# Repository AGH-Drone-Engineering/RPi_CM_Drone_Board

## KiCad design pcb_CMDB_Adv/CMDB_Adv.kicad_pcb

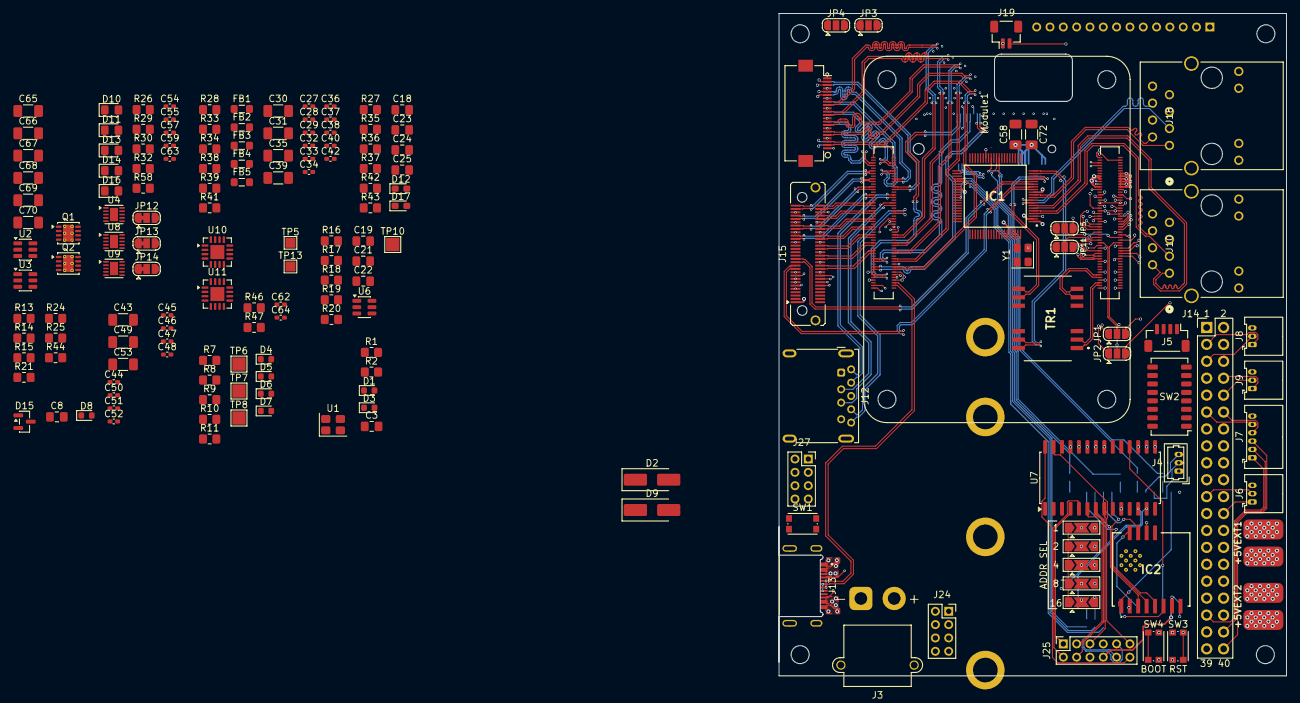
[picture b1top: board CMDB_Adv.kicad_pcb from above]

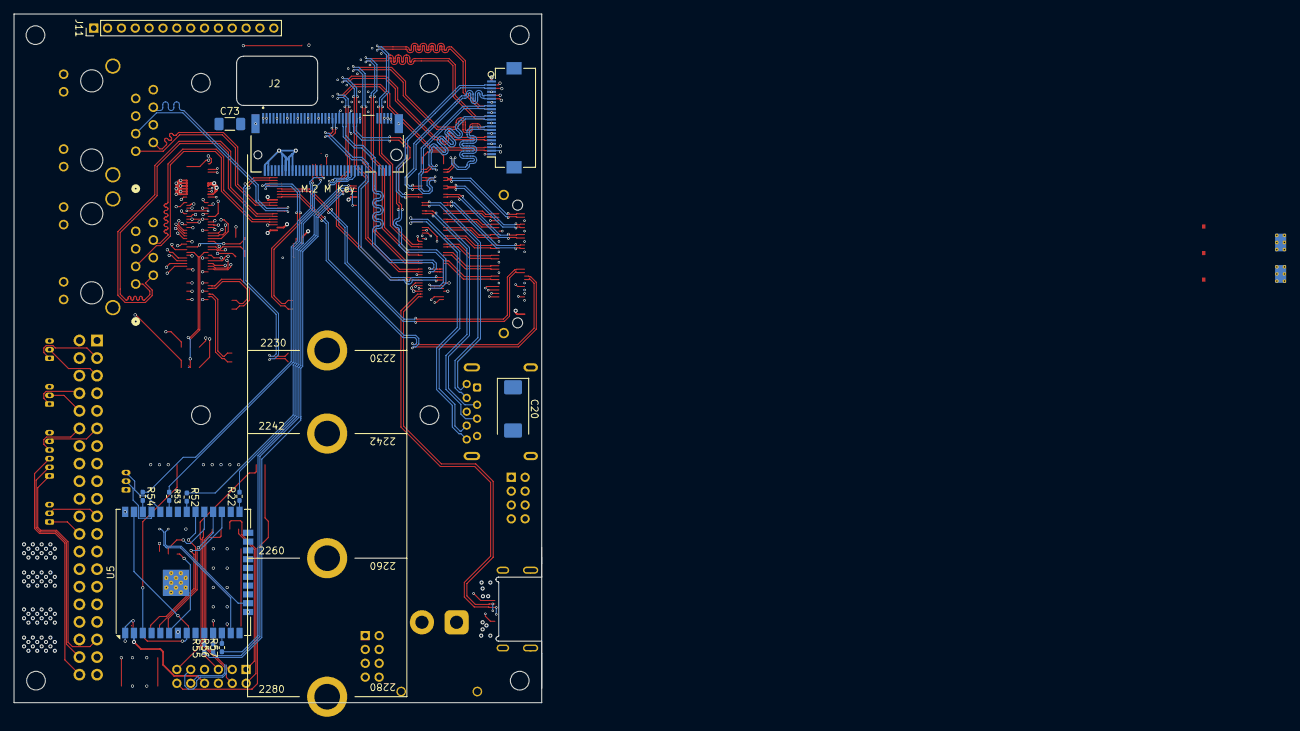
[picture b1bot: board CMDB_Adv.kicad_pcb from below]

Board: 6 copper layers, 76.2 x 99.4 mm, 190 parts (13 on the bottom side), 277 nets.

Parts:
C3, C18, C23, C24, C25: 100n; C_0805_2012Metric_Pad1.18x1.45mm_HandSolder
C8: 470nF; C_0805_2012Metric_Pad1.18x1.45mm_HandSolder
C19, C21, C22: 10u; C_0805_2012Metric_Pad1.18x1.45mm_HandSolder
C20: 100uF; CP_EIA-7343-31_Kemet-D
C27, C28, C29, C32, C33, C34, C36, C37, C38, C40, C42, C44, C45, C46, C47, C48, C50, C51, C52, C54, C55, C57, C59, C62, C63, C64: 100nF; C_0402_1005Metric_Pad0.74x0.62mm_HandSolder
C30, C31, C35, C39, C43, C49, C58, C72, C73: 22uF; C_1206_3216Metric_Pad1.33x1.80mm_HandSolder
C53, C65, C66, C67, C68, C69, C70: 10uF; C_1206_3216Metric_Pad1.33x1.80mm_HandSolder
D1, D8: LED Green; LED_0603_1608Metric
D2, D9: SS34; D_SMA_Handsoldering
D3: LED Red; LED_0603_1608Metric
D4, D6: GREEN; LED_0603_1608Metric
D5: RED; LED_0603_1608Metric
D7: AMBER; LED_0603_1608Metric
D10: PWR_VALID; D_0805_2012Metric_Pad1.15x1.40mm_HandSolder
D11: +5VPB; D_0805_2012Metric_Pad1.15x1.40mm_HandSolder
D12: ETH4_Y; LED_0603_1608Metric_Pad1.05x0.95mm_HandSolder
D13: +5VEXT1; D_0805_2012Metric_Pad1.15x1.40mm_HandSolder
D14: +5VEXT2; D_0805_2012Metric_Pad1.15x1.40mm_HandSolder
D15: BAT54A; SOT-23
D16: +VIMM; D_0805_2012Metric_Pad1.15x1.40mm_HandSolder
D17: ETH4_G; LED_0603_1608Metric_Pad1.05x0.95mm_HandSolder
FB1, FB2, FB3, FB4, FB5: BLM21PG221SN1D; L_0805_2012Metric_Pad1.05x1.20mm_HandSolder
H1, H2, H3, H4: MountingHole; MountingHole_2.7mm_M2.5_DIN965
IC1: KSZ8795CLXCC; QFP40P1200X1200X160-80N
IC2: Wio-SX1262
J2: Bus_M.2_Socket_M; M.2_M_Key_socket_2280
J3: CONN_VIN; AMASS_XT30PW-M_1x02_P2.50mm_Horizontal
J4: J_ESP_DBG_UART; Molex_PicoBlade_53047-0310_1x03_P1.25mm_Vertical
J5: CONN_FAN; JST_SH_BM04B-SRSS-TB_1x04-1MP_P1.00mm_Vertical
J6: CONN_UART2; Molex_PicoBlade_53048-0310_1x03_P1.25mm_Horizontal
J7: CONN_SPI1; Molex_PicoBlade_53048-0610_1x06_P1.25mm_Horizontal
J8: CONN_I2C1; Molex_PicoBlade_53048-0310_1x03_P1.25mm_Horizontal
J9: CONN_UART0; Molex_PicoBlade_53048-0310_1x03_P1.25mm_Horizontal
J10: ETH1; CONN12_ARJM11B1-009-AB-EW2_ABR
J11: CONN_SDIO; PinHeader_1x14_P2.00mm_Vertical
J12: CONN_USB3_A; USB3_A_Molex_48393-001
J13: CONN_USB_PWR_OTG; GCT_USB4510-03-1-A_REVA
J14: CONN_HAT; PinHeader_2x20_P2.54mm_Vertical
J15: CONN_DOCK; Samtec_LSHM-130-xx.x-x-DV-S_2x30-1SH_P0.50mm_Vertical
J16: CONN_CAM1; Hirose_FH12-22S-0.5SH_1x22-1MP_P0.50mm_Horizontal
J17: CONN_CAM0; Hirose_FH12-22S-0.5SH_1x22-1MP_P0.50mm_Horizontal
J18: ETH2; CONN12_ARJM11B1-009-AB-EW2_ABR
J19: CONN_RTC; JST_SH_BM02B-SRSS-TB_1x02-1MP_P1.00mm_Vertical
J20: CONN_5VEXT1; SolderWirePad_1x01_SMD_3x6mm
J21: CONN_5VEXT1_GND; SolderWirePad_1x01_SMD_3x6mm
J22: CONN_5VEXT2; SolderWirePad_1x01_SMD_3x6mm
J23: CONN_5VEXT2_GND; SolderWirePad_1x01_SMD_3x6mm
J24: AUX_PWR_OUT1; PinSocket_2x04_P2.00mm_Vertical
J25: PL_CTRL_IO; PinSocket_2x06_P2.00mm_Vertical
J27: AUX_PWR_OUT2; PinSocket_2x04_P2.00mm_Vertical
JP1: GPIO0_SEL; SolderJumper-3_P1.3mm_Open_RoundedPad1.0x1.5mm
JP2: GPIO1_SEL; SolderJumper-3_P1.3mm_Open_RoundedPad1.0x1.5mm
JP3: ETH_Y_SEL; SolderJumper-3_P1.3mm_Open_RoundedPad1.0x1.5mm
JP4: ETH_G_SEL; SolderJumper-3_P1.3mm_Open_RoundedPad1.0x1.5mm
JP5: GPIO8_SEL; SolderJumper-3_P1.3mm_Open_RoundedPad1.0x1.5mm
JP6: ADDR1; SolderJumper-3_P2.0mm_Open_TrianglePad1.0x1.5mm
JP7: ADDR2; SolderJumper-3_P2.0mm_Open_TrianglePad1.0x1.5mm
JP8: ADDR4; SolderJumper-3_P2.0mm_Open_TrianglePad1.0x1.5mm
JP9: ADDR8; SolderJumper-3_P2.0mm_Open_TrianglePad1.0x1.5mm
JP10: ADDR16; SolderJumper-3_P2.0mm_Open_TrianglePad1.0x1.5mm
JP11: GPIO9_SEL; SolderJumper-3_P1.3mm_Open_RoundedPad1.0x1.5mm
JP12: +3V3PB2 DIS; SolderJumper-3_P1.3mm_Bridged12_RoundedPad1.0x1.5mm
JP13: +3V3PB3 DIS; SolderJumper-3_P1.3mm_Bridged12_RoundedPad1.0x1.5mm
JP14: +1V2PB DIS; SolderJumper-3_P1.3mm_Bridged12_RoundedPad1.0x1.5mm
Module1: ComputeModule5-CM5; Raspberry-Pi-5-Compute-Module
Q1, Q2: AON7534; DFN-8-1EP_3x3mm_P0.65mm_EP1.6x2.56mm_ThermalVias
R1, R2, R7, R8, R9, R10, R13, R21, R26, R29, R30, R32, R34, R39, R41, R42, R43, R46, R47, R58: 1K; R_0805_2012Metric_Pad1.20x1.40mm_HandSolder
R11, R44: 10K; R_0805_2012Metric_Pad1.20x1.40mm_HandSolder
R14, R15, R38: 4K7; R_0805_2012Metric_Pad1.20x1.40mm_HandSolder
R16, R18, R19, R20: 2.2K; R_0805_2012Metric_Pad1.20x1.40mm_HandSolder
R17: 15K; R_0805_2012Metric_Pad1.20x1.40mm_HandSolder
R22, R52, R53, R54, R55, R56, R57: 22R; R_0402_1005Metric_Pad0.72x0.64mm_HandSolder
R24, R25: 2K2; R_0805_2012Metric_Pad1.20x1.40mm_HandSolder
R27, R35, R36, R37: 220R; R_0805_2012Metric_Pad1.20x1.40mm_HandSolder
R28: 12K4 1%; R_0805_2012Metric_Pad1.20x1.40mm_HandSolder
R33: 330R; R_0805_2012Metric_Pad1.20x1.40mm_HandSolder
SW1: BT_PWR; SW_Push_1P1T_NO_CK_KMR2
SW2: SW_CONFIG; SW_DIP_SPSTx08_Slide_Copal_CHS-08A_W5.08mm_P1.27mm_JPin
SW3: SW_RESET; SW_Push_1P1T_NO_CK_KMR2
SW4: SW_BOOT; SW_Push_1P1T_NO_CK_KMR2
TP5: PWR_VALID0; TestPoint_Pad_1.5x1.5mm
TP6: +3V3 RPi; TestPoint_Pad_2.0x2.0mm
TP7: TP nPWR; TestPoint_Pad_2.0x2.0mm
TP8: TP nACT; TestPoint_Pad_2.0x2.0mm
TP10: TP VBUS_USB; TestPoint_Pad_2.0x2.0mm
TP13: PWR_VALID1; TestPoint_Pad_1.5x1.5mm
TR1: ALANL100X1-DE12DT; ALANL100X1DE12DT
U1: ASEK-32.768KHZ-L-R-T; Crystal_SMD_3225-4Pin_3.2x2.5mm
U2, U3: LM74700; SOT-23-6
U4, U8, U9: TPS7A91; Texas_S-PDSO-N10_EP1.2x2mm
U5: ESP32-WROOM-32UE
U6: AP22653W6; SOT-23-6
U7: MCP23017_SO; SOIC-28W_7.5x17.9mm_P1.27mm
U10, U11: INA3221; Texas_RGV0016A_VQFN-16-1EP_4x4mm_P0.65mm_EP2.1x2.1mm
Y1: ASE-25.000MHZ-LC-T; Oscillator_SMD_Abracon_ASE-4Pin_3.2x2.5mm

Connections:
/+1V2PB: C66.1, FB3.1, FB4.1, U9.1 (OUT), U9.2 (OUT)
/+3V3PB1: C3.1, C58.2, C72.2, C73.2, D1.2 (A), D3.2 (A), J2.2 (3.3V), J2.4 (3.3V), J2.12 (3.3V), J2.14 (3.3V), J2.16 (3.3V), J2.18 (3.3V), J2.70 (3.3V), J2.72 (3.3V), J2.74 (3.3V), U1.1 (EN), U1.4 (VDD)
/+3V3PB2: C49.2, C50.2, C51.2, C52.2, C67.1, D15.1, FB1.1, FB2.1, J25.8, R13.1, R14.1, R15.1, R24.1, R25.1, R44.2, U4.1 (OUT), U4.2 (OUT), U5.2 (VDD), U7.9 (V_{DD})
/+3V3PB3: C43.2, C44.2, C68.1, IC2.8 (VCC), U8.1 (OUT), U8.2 (OUT)
/+5VEXT1: D13.2 (A), J20.1 (Pin_1_1)
/+5VEXT2: D14.2 (A), J22.1 (Pin_1_1)
/+5VPB: C19.1, D11.2 (A), J5.1, J14.2, J14.4, J15.1, Module1.77 (+5v_(Input)), Module1.79 (+5v_(Input)), Module1.81 (+5v_(Input)), Module1.83 (+5v_(Input)), Module1.85 (+5v_(Input)), Module1.87 (+5v_(Input)), Q1.1 (D), Q2.1 (D), U2.4 (CATHODE), U3.4 (CATHODE), U6.1 (IN)
/+VBUS_USBC: C55.2, D2.2 (A), J13.A4_B9 (VBUS), J13.B4_A9 (VBUS), Q2.3 (S), R16.1, U3.3 (EN), U3.6 (ANODE)
/CM5/+3V3RPi: D4.2 (A), D5.2 (A), D6.2 (A), D7.2 (A), J11.1, J14.1, J14.17, J15.3, J16.22, J17.22, Module1.78 (GPIO_VREF(1.8v/3.3v_Input)), Module1.84 (+3.3v_(Output)), Module1.86 (+3.3v_(Output)), R11.1, R18.2, R19.2, R20.1, R27.2, R35.2, R36.2, R37.2, R42.2, R43.2, TP6.1 (1_1)
/CM5/+3V3STB: J19.2, Module1.76 (VBAT)
/CM5/BT_nDis: Module1.91 (BT_nDisable), SW2.11
/CM5/CAM0_GPIO0: J17.17, Module1.97 (CAM_GPIO0)
/CM5/CAM0_GPIO1: J17.18, Module1.100 (CAM_GPIO1)
/CM5/EEPROM_nWP: Module1.20 (EEPROM_nWP), SW2.15
/CM5/ETH.P0_N: Module1.10 (Ethernet_Pair0_N), TR1.6 (RD-)
/CM5/ETH.P0_P: Module1.12 (Ethernet_Pair0_P), TR1.5 (RD+)
/CM5/ETH.P1_N: Module1.6 (Ethernet_Pair1_N), TR1.2 (TD-)
/CM5/ETH.P1_P: Module1.4 (Ethernet_Pair1_P), TR1.1 (TD+)
/CM5/ETH_LED_G: JP4.2 (C), R9.2
/CM5/ETH_LED_Y: JP3.2 (C), R10.2
/CM5/FAN_PWM: J5.2, Module1.19 (FAN_PWM), R11.2
/CM5/GP.0: J14.27, JP1.3 (B)
/CM5/GP.1: J14.28, JP2.3 (B)
/CM5/GP.2: J8.1, J14.3, Module1.58 (GPIO2)
/CM5/GP.3: J8.2, J14.5, Module1.56 (GPIO3)
/CM5/GP.4: J6.1, J14.7, Module1.54 (GPIO4)
/CM5/GP.5: J6.2, J14.29, Module1.34 (GPIO5)
/CM5/GP.6: J14.31, Module1.30 (GPIO6)
/CM5/GP.7: J14.26, Module1.37 (GPIO7)
/CM5/GP.8: J14.24, JP5.3 (B)
/CM5/GP.9: J14.21, JP11.3 (B)
/CM5/GP.10: J14.19, Module1.44 (GPIO10)
/CM5/GP.11: J14.23, Module1.38 (GPIO11)
/CM5/GP.12: J14.32, Module1.31 (GPIO12)
/CM5/GP.13: J14.33, Module1.28 (GPIO13)
/CM5/GP.14: J9.1, J14.8, Module1.55 (GPIO14)
/CM5/GP.15: J9.2, J14.10, Module1.51 (GPIO15)
/CM5/GP.16: J14.36, Module1.29 (GPIO16)
/CM5/GP.17: J7.5, J14.11, Module1.50 (GPIO17)
/CM5/GP.18: J7.4, J14.12, Module1.49 (GPIO18)
/CM5/GP.19: J7.1, J14.35, Module1.26 (GPIO19)
/CM5/GP.20: J7.2, J14.38, Module1.27 (GPIO20)
/CM5/GP.21: J7.3, J14.40, Module1.25 (GPIO21)
/CM5/GP.22: J14.15, Module1.46 (GPIO22)
/CM5/GP.23: J14.16, Module1.47 (GPIO23)
/CM5/GP.24: J14.18, Module1.45 (GPIO24)
/CM5/GP.25: J14.22, Module1.41 (GPIO25)
/CM5/GP.26: J14.37, Module1.24 (GPIO26)
/CM5/GP.27: J14.13, Module1.48 (GPIO27)
/CM5/GPIO0_RAW: JP1.2 (C), Module1.36 (ID_SD)
/CM5/GPIO1_RAW: JP2.2 (C), Module1.35 (ID_SC)
/CM5/GPIO8_RAW: JP5.2 (C), Module1.39 (GPIO8)
/CM5/GPIO9_RAW: JP11.2 (C), Module1.40 (GPIO9)
/CM5/HDMI0.CEC: J15.15, Module1.151 (HDMI0_CEC)
/CM5/HDMI0.CK_N: J15.59, Module1.190 (HDMI0_CLK_N)
/CM5/HDMI0.CK_P: J15.57, Module1.188 (HDMI0_CLK_P)
/CM5/HDMI0.D0_N: J15.53, Module1.184 (HDMI0_TX0_N)
/CM5/HDMI0.D0_P: J15.51, Module1.182 (HDMI0_TX0_P)
/CM5/HDMI0.D1_N: J15.47, Module1.178 (HDMI0_TX1_N)
/CM5/HDMI0.D1_P: J15.45, Module1.176 (HDMI0_TX1_P)
/CM5/HDMI0.D2_N: J15.41, Module1.172 (HDMI0_TX2_N)
/CM5/HDMI0.D2_P: J15.39, Module1.170 (HDMI0_TX2_P)
/CM5/HDMI0.HP: J15.17, Module1.153 (HDMI0_HOTPLUG)
/CM5/HDMI0.SCL: J15.11, Module1.200 (HDMI0_SCL)
/CM5/HDMI0.SDA: J15.13, Module1.199 (HDMI0_SDA)
/CM5/HDMI1.CEC: J15.16, Module1.149 (HDMI1_CEC)
/CM5/HDMI1.CK_N: J15.60, Module1.166 (HDMI1_CLK_N)
/CM5/HDMI1.CK_P: J15.58, Module1.164 (HDMI1_CLK_P)
/CM5/HDMI1.D0_N: J15.54, Module1.160 (HDMI1_TX0_N)
/CM5/HDMI1.D0_P: J15.52, Module1.158 (HDMI1_TX0_P)
/CM5/HDMI1.D1_N: J15.48, Module1.154 (HDMI1_TX1_N)
/CM5/HDMI1.D1_P: J15.46, Module1.152 (HDMI1_TX1_P)
/CM5/HDMI1.D2_N: J15.42, Module1.148 (HDMI1_TX2_N)
/CM5/HDMI1.D2_P: J15.40, Module1.146 (HDMI1_TX2_P)
/CM5/HDMI1.HP: J15.18, Module1.143 (HDMI1_HOTPLUG)
/CM5/HDMI1.SCL: J15.12, Module1.147 (HDMI1_SCL)
/CM5/HDMI1.SDA: J15.14, Module1.145 (HDMI1_SDA)
/CM5/MIPI0.CK_N: J17.8, Module1.127 (MIPI0_C_N)
/CM5/MIPI0.CK_P: J17.9, Module1.129 (MIPI0_C_P)
/CM5/MIPI0.D0_N: J17.2, Module1.115 (MIPI0_D0_N)
/CM5/MIPI0.D0_P: J17.3, Module1.117 (MIPI0_D0_P)
/CM5/MIPI0.D1_N: J17.5, Module1.121 (MIPI0_D1_N)
/CM5/MIPI0.D1_P: J17.6, Module1.123 (MIPI0_D1_P)
/CM5/MIPI0.D2_N: J17.11, Module1.133 (MIPI0_D2_N)
/CM5/MIPI0.D2_P: J17.12, Module1.135 (MIPI0_D2_P)
/CM5/MIPI0.D3_N: J17.14, Module1.139 (MIPI0_D3_N)
/CM5/MIPI0.D3_P: J17.15, Module1.141 (MIPI0_D3_P)
/CM5/MIPI0_ID_SCL: J17.20, Module1.80 (SCL0)
/CM5/MIPI0_ID_SDA: J17.21, Module1.82 (SDA0)
/CM5/MIPI1.CK_N: J16.8, Module1.187 (MIPI1_C_N)
/CM5/MIPI1.CK_P: J16.9, Module1.189 (MIPI1_C_P)
/CM5/MIPI1.D0_N: J16.2, Module1.175 (MIPI1_D0_N)
/CM5/MIPI1.D0_P: J16.3, Module1.177 (MIPI1_D0_P)
/CM5/MIPI1.D1_N: J16.5, Module1.181 (MIPI1_D1_N)
/CM5/MIPI1.D1_P: J16.6, Module1.183 (MIPI1_D1_P)
/CM5/MIPI1.D2_N: J16.11, Module1.193 (MIPI1_D2_N)
/CM5/MIPI1.D2_P: J16.12, Module1.195 (MIPI1_D2_P)
/CM5/MIPI1.D3_N: J16.14, Module1.194 (MIPI1_D3_N)
/CM5/MIPI1.D3_P: J16.15, Module1.196 (MIPI1_D3_P)
/CM5/MIPI1_ID_SCL: J16.20, JP2.1 (A), R19.1
/CM5/MIPI1_ID_SDA: J16.21, JP1.1 (A), R18.1
/CM5/PCIe.CLK_N: J2.53 (REFCLKn), Module1.112 (PCIe_CLK_N)
/CM5/PCIe.CLK_P: J2.55 (REFCLKp), Module1.110 (PCIe_CLK_P)
/CM5/PCIe.RX_N: J2.41 (PETn0), Module1.118 (PCIe_RX_N)
/CM5/PCIe.RX_P: J2.43 (PETp0), Module1.116 (PCIe_RX_P)
/CM5/PCIe.TX_N: J2.47 (PERn0), Module1.124 (PCIe_TX_N)
/CM5/PCIe.TX_P: J2.49 (PERp0), Module1.122 (PCIe_TX_P)
/CM5/PCIe.nCLKREQ: J2.52 (~CLKREQ), Module1.102 (PCIe_nCLKREQ)
/CM5/PCIe.nRST: J2.50 (~PERST), Module1.109 (PCIe_nRST)
/CM5/PCIe.nWAKE: J2.54 (~PEWAKE), Module1.104 (PCIE_nWAKE)
/CM5/PMIC_ENABLE: Module1.99 (PMIC_ENABLE), SW2.13
/CM5/PWR_BUT: Module1.92 (PWR_BUT), SW1.2
/CM5/RPI_ETH_G: JP4.1 (A), Module1.15 (Ethernet_nLED3(3.3v))
/CM5/RPI_ETH_Y: JP3.1 (A), Module1.17 (Ethernet_nLED2(3.3v))
/CM5/SD.CLK: J11.12, Module1.57 (SD_CLK)
/CM5/SD.CMD: J11.13, Module1.62 (SD_CMD)
/CM5/SD.DAT0: J11.3, Module1.63 (SD_DAT0)
/CM5/SD.DAT1: J11.4, Module1.67 (SD_DAT1)
/CM5/SD.DAT2: J11.5, Module1.69 (SD_DAT2)
/CM5/SD.DAT3: J11.6, Module1.61 (SD_DAT3)
/CM5/SD.DAT4: J11.8, Module1.68 (SD_DAT4)
/CM5/SD.DAT5: J11.9, Module1.64 (SD_DAT5)
/CM5/SD.DAT6: J11.10, Module1.72 (SD_DAT6)
/CM5/SD.DAT7: J11.11, Module1.70 (SD_DAT7)
/CM5/SD.PWR_EN: J11.2, Module1.75 (SD_PWR_ON)
/CM5/TACHO: J5.4, Module1.16 (FAN_TACHO)
/CM5/UART_PCTL_RX: JP11.1 (A), U5.23 (IO15)
/CM5/UART_PCTL_TX: JP5.1 (A), U5.4 (SENSOR_VP)
/CM5/USB0.D_N: J15.30, Module1.136 (USB3-0-D_N)
/CM5/USB0.D_P: J15.28, Module1.134 (USB3-0-D_P)
/CM5/USB0.RX_N: J15.22, Module1.128 (USB3-0-RX_N)
/CM5/USB0.RX_P: J15.24, Module1.130 (USB3-0-RX_P)
/CM5/USB0.TX_N: J15.34, Module1.140 (USB3-0-TX_N)
/CM5/USB0.TX_P: J15.36, Module1.142 (USB3-0-TX_P)
/CM5/USB1.D_N: J12.2 (D-), Module1.165 (USB3-1-D_N)
/CM5/USB1.D_P: J12.3 (D+), Module1.163 (USB3-1-D_P)
/CM5/USB1.RX_N: J12.5 (SSRX-), Module1.157 (USB3-1-RX_N)
/CM5/USB1.RX_P: J12.6 (SSRX+), Module1.159 (USB3-1-RX_P)
/CM5/USB1.TX_N: J12.8 (SSTX-), Module1.169 (USB3-1-TX_N)
/CM5/USB1.TX_P: J12.9 (SSTX+), Module1.171 (USB3-1-TX_P)
/CM5/USBC.CC1: J13.A5 (CC1), Module1.94 (CC1)
/CM5/USBC.CC2: J13.B5 (CC2), Module1.96 (CC2)
/CM5/USBC.D_N: J13.A7 (D-), J13.B7 (D-), Module1.103 (USB2_N)
/CM5/USBC.D_P: J13.A6 (D+), J13.B6 (D+), Module1.105 (USB2_P)
/CM5/USBOTG: Module1.101 (USB_OTG_ID), SW2.14
/CM5/VBUS_USBA_EN: Module1.111 (VBUS_EN), U6.3 (EN)
/CM5/WL_nDis: Module1.89 (WiFi_nDisable), SW2.12
/CM5/nACT_LED: Module1.21 (LED_nACT), R7.2, TP8.1 (1_1)
/CM5/nPWR_LED: Module1.95 (LED_nPWR), R8.2, TP7.1 (1_1)
/CM5/nRPIBOOT: Module1.93 (nRPIBOOT), SW2.16
/ETH3.LED_G: D17.1 (K), R41.1
/ETH3.LED_Y: D12.1 (K), R34.2, R39.1
/ETH3.RX_N: IC1.14 (RXM3), J15.23
/ETH3.RX_P: IC1.13 (RXP3), J15.21
/ETH3.TX_N: IC1.16 (TXM3), J15.27
/ETH3.TX_P: IC1.15 (TXP3), J15.25
/Eth Switch/+VDD12A: C39.2, C40.2, FB4.2, IC1.1 (VDD12A)
/Eth Switch/+VDD12D: C35.2, C36.2, C37.2, C38.2, FB3.2, IC1.26 (VDD12D_1), IC1.42 (VDD12D_2), IC1.73 (VDD12D_3)
/Eth Switch/+VDDAT: C27.2, C28.2, C29.2, C30.2, FB1.2, FB5.1, IC1.2 (VDDAT33_1), IC1.12 (VDDAT33_2), IC1.76 (VDDAT33_3)
/Eth Switch/+VDDIO: C31.2, C32.2, C33.2, C34.2, FB2.2, IC1.34 (VDDIO_1), IC1.48 (VDDIO_2), IC1.70 (VDDIO_3), R38.1
/Eth Switch/+VDDOSC: C42.2, FB5.2, Y1.1 (EN), Y1.4 (Vdd)
/Eth Switch/ETH1.LED_G: IC1.65 (LED1_0), J10.10
/Eth Switch/ETH1.LED_Y: IC1.64 (LED1_1), J10.11
/Eth Switch/ETH1.RX_N: IC1.5 (RXM1), J10.6 (RD-)
/Eth Switch/ETH1.RX_P: IC1.4 (RXP1), J10.3 (RD+)
/Eth Switch/ETH1.TX_N: IC1.7 (TXM1), J10.2 (TD-)
/Eth Switch/ETH1.TX_P: IC1.6 (TXP1), J10.1 (TD+)
/Eth Switch/ETH2.LED_G: IC1.63 (LED2_0), J18.10
/Eth Switch/ETH2.LED_Y: IC1.62 (LED2_1), J18.11
/Eth Switch/ETH2.RX_N: IC1.9 (RXM2), J18.6 (RD-)
/Eth Switch/ETH2.RX_P: IC1.8 (RXP2), J18.3 (RD+)
/Eth Switch/ETH2.TX_N: IC1.11 (TXM2), J18.2 (TD-)
/Eth Switch/ETH2.TX_P: IC1.10 (TXP2), J18.1 (TD+)
/Eth Switch/ETH4.RX_N: IC1.18 (RXM4), TR1.7 (RX-)
/Eth Switch/ETH4.RX_P: IC1.17 (RXP4), TR1.8 (RX+)
/Eth Switch/ETH4.TX_N: IC1.20 (TXM4), TR1.11 (TX-)
/Eth Switch/ETH4.TX_P: IC1.19 (TXP4), TR1.12 (TX+)
/Eth Switch/MGMT_SPI.CS: IC1.69 (SPIS_N), U5.9 (IO33)
/Eth Switch/MGMT_SPI.MISO: IC1.66 (SPIQ), IC2.2 (MISO), R33.2, U5.7 (IO35)
/Eth Switch/MGMT_SPI.MOSI: IC1.68 (SDA_MDIO), IC2.3 (MOSI), U5.28 (IO17)
/Eth Switch/MGMT_SPI.SCLK: IC1.67 (SCL_MDC), IC2.4 (SCK), U5.30 (IO18)
/Eth Switch/RMII.CRS_DV: IC1.51 (RXDV5/CRSDV5/RXD5_CTL), R57.1
/Eth Switch/RMII.REFCLK: IC1.44 (RXC5/GRXC5), R22.2
/Eth Switch/RMII.RXD0: IC1.45 (RXD5_0), R55.1
/Eth Switch/RMII.RXD1: IC1.46 (RXD5_1), R56.1
/Eth Switch/RMII.TXD0: IC1.30 (TXD5_0), R52.1
/Eth Switch/RMII.TXD1: IC1.32 (TXD5_1), R54.1
/Eth Switch/RMII.TX_EN: IC1.29 (TXEN5/TXDS5_CTL), R53.1
/Eth Switch/RST_N: C53.1, D15.3, IC1.72 (RST_N), R44.1, U5.26 (IO4)
/Eth Switch/SWITCH_INT: IC1.23 (INTR_N), R38.2, U5.5 (SENSOR_VN)
/IO Connectors/+VBUS_USBA: C20.1, C21.1, C22.1, J12.1 (VBUS), J15.2, J15.4, TP10.1 (1_1), U6.6 (OUT)
/IO Connectors/CAM1_GPIO0: J16.17, R20.2
/IO Connectors/PCTL_DBG_UART_RX: J4.3, J15.7, U5.34 (RXD0/IO3)
/IO Connectors/PCTL_DBG_UART_TX: J4.2, J15.5, U5.35 (TXD0/IO1)
/PSU/+VIMM: C65.1, C69.1, C70.1, D2.1 (K), D9.1 (K), D16.2 (A), JP12.1 (A), JP13.1 (A), JP14.1 (A), U4.9 (IN), U4.10 (IN), U8.9 (IN), U8.10 (IN), U9.9 (IN), U9.10 (IN)
/PSU/+VIN: J3.2, J24.4, J24.5, J24.6, J24.7, J24.8
/PSU/PSU Converters/+5VPB: C54.2, J27.5, J27.6, Q1.3 (S), U2.3 (EN), U2.6 (ANODE)
/PSU/PSU Converters/+I2C_SCL: U10.6 (SCL), U11.6 (SCL)
/PSU/PSU Converters/+I2C_SDA: U10.7 (SDA), U11.7 (SDA)
/PSU/PSU Converters/+VIMM: C62.2, C64.2, D9.2 (A), J27.7, J27.8, U10.4 (VS), U11.4 (VS), U11.5 (A0)
/PSU/PSU Converters/POWER_VALID0: R46.2, TP5.1 (1_1), U10.10 (PV)
/PSU/PSU Converters/POWER_VALID1: R47.2, TP13.1 (1_1), U11.10 (PV)
/Platform Controller/ADDR1: JP6.2 (C), U7.21 (GPA0)
/Platform Controller/ADDR2: JP7.2 (C), U7.22 (GPA1)
/Platform Controller/ADDR4: JP8.2 (C), U7.23 (GPA2)
/Platform Controller/ADDR8: JP9.2 (C), U7.24 (GPA3)
/Platform Controller/ADDR16: JP10.2 (C), U7.25 (GPA4)
/Platform Controller/ADDR_HIGH: JP6.1 (A), JP7.1 (A), JP8.1 (A), JP9.1 (A), JP10.1 (A), R13.2
/Platform Controller/BOOT_MODE: R15.2, R22.1, SW4.2, U5.25 (IO0)
/Platform Controller/ENABLE: C8.2, D15.2, R14.2, SW3.2, U5.3 (EN), U7.18 (~RESET)
/Platform Controller/I2C_SCL: J25.9, R25.2, U5.16 (IO13), U7.12 (SCK)
/Platform Controller/I2C_SDA: J25.10, R24.2, U5.13 (IO14), U7.13 (SDA)
/Platform Controller/LED_ACT: R21.1, U7.26 (GPA5)
/Platform Controller/LORA_BUSY: IC2.11 (BUSY), U5.29 (IO5)
/Platform Controller/LORA_CS: IC2.6 (NSS), U5.8 (IO32)
/Platform Controller/LORA_DIO1: IC2.12 (DIO1), U5.6 (IO34)
/Platform Controller/LORA_RESET: IC2.5 (NRST), U5.27 (IO16)
/Platform Controller/LORA_RF_SW: IC2.1 (RF_SW_), U5.37 (IO23)
GND: C3.2, C8.1, C18.2, C19.2, C20.2, C21.2, C22.2, C23.2, C24.2, C25.2, C27.1, C28.1, C29.1, C30.1, C31.1, C32.1, C33.1, C34.1, C35.1, C36.1, C37.1, C38.1, C39.1, C40.1, C42.1, C43.1, C44.1, C45.2, C46.2, C47.2, C48.2, C49.1, C50.1, C51.1, C52.1, C53.2, C57.1, C58.1, C59.1, C62.1, C63.1, C64.1, C65.2, C66.2, C67.2, C68.2, C69.2, C70.2, C72.1, C73.1, D8.1 (K), IC1.3 (GNDA_1), IC1.21 (GNDA_2), IC1.27 (GNDD_1), IC1.33 (GNDD_2), IC1.47 (GNDD_3), IC1.61 (GNDD_4), IC1.71 (GNDD_5), IC1.78 (GNDA_3), IC2.7 (GND_1), IC2.10 (GND_2), J2.1 (GND), J2.3 (GND), J2.9 (GND), J2.15 (GND), J2.21 (GND), J2.27 (GND), J2.33 (GND), J2.39 (GND), J2.45 (GND), J2.51 (GND), J2.57 (GND), J2.71 (GND), J2.73 (GND), J2.75 (GND), J2.M1 (GND2230), J2.M2 (GND2242), J2.M3 (GND2260), J2.M4 (GND2280), J2.S1, J2.S2, J3.1, J4.1, J5.3, J6.3, J7.6, J8.3, J9.3, J10.8, J11.7, J11.14, J12.4 (GND), J12.7 (DRAIN), J12.10 (SHIELD), J13.A1_B12 (GND), J13.B1_A12 (GND), J13.S1 (SHIELD), J13.S2 (SHIELD), J13.S3 (SHIELD), J13.S4 (SHIELD), J14.6, J14.9, J14.14, J14.20, J14.25, J14.30, J14.34, J14.39, J15.9, J15.10, J15.19, J15.20, J15.26, J15.32, J15.37, J15.38, J15.43, J15.44, J15.49, J15.50, J15.55, J15.56, J15.SH (Shield), J16.1, J16.4, J16.7, J16.10, J16.13, J16.16, J16.19, J17.1, J17.4, J17.7, J17.10, J17.13, J17.16, J17.19, J18.8, J19.1, J21.1 (Pin_1_1), J23.1 (Pin_1_1), J24.1, J24.2, J24.3, J25.6, J25.7, J27.1, J27.2, J27.3, J27.4, JP6.3 (B), JP7.3 (B), JP8.3 (B), JP9.3 (B), JP10.3 (B), JP12.3 (B), JP13.3 (B), JP14.3 (B), Module1.1 (GND), Module1.2 (GND), Module1.7 (GND), Module1.8 (GND), Module1.13 (GND), Module1.14 (GND), Module1.22 (GND), Module1.23 (GND), Module1.32 (GND), Module1.33 (GND), Module1.42 (GND), Module1.43 (GND), Module1.52 (GND), Module1.53 (GND), Module1.59 (GND), Module1.60 (GND), Module1.65 (GND), Module1.66 (GND), Module1.71 (GND), Module1.74 (GND), Module1.98 (GND), Module1.107 (GND), Module1.108 (GND), Module1.113 (GND), Module1.114 (GND), Module1.119 (GND), Module1.120 (GND), Module1.125 (GND), Module1.126 (GND), Module1.131 (GND), Module1.132 (GND), Module1.137 (GND), Module1.138 (GND), Module1.144 (GND), Module1.150 (GND), Module1.155 (GND), Module1.156 (GND), Module1.161 (GND), Module1.162 (GND), Module1.167 (GND), Module1.168 (GND), Module1.173 (GND), Module1.174 (GND), Module1.179 (GND), Module1.180 (GND), Module1.185 (GND), Module1.186 (GND), Module1.191 (GND), Module1.192 (GND), Module1.197 (GND), Module1.198 (GND), R2.2, R16.2, R17.2, R26.2, R28.1, R29.2, R30.2, R32.2, R33.1, R34.1, R58.2, SW1.1, SW2.1, SW2.2, SW2.3, SW2.4, SW2.5, SW2.6, SW2.7, SW2.8, SW3.1, SW4.1, U1.2 (GND), U2.2 (GND), U3.2 (GND), U4.4 (GND), U4.6 (SS_CTRL), U4.11 (GND), U5.1 (GND), U5.15 (GND), U5.38 (GND), U5.39 (GND), U6.2 (GND), U7.10 (V_{SS}), U7.15 (A0), U7.16 (A1), U7.17 (A2), U8.4 (GND), U8.6 (SS_CTRL), U8.11 (GND), U9.4 (GND), U9.6 (SS_CTRL), U9.11 (GND), U10.3 (GND), U10.5 (A0), U10.17 (EP), U11.3 (GND), U11.17 (EP), Y1.2 (GND)
unnamed: D1.1 (K), R1.1
unnamed: D3.1 (K), R2.1
unnamed: D4.1 (K), R7.1
unnamed: D5.1 (K), R8.1
unnamed: D6.1 (K), R9.1
unnamed: D7.1 (K), R10.1
unnamed: D8.2 (A), R21.2
unnamed: D10.1 (K), R26.1
unnamed: D11.1 (K), R58.1
unnamed: D12.2 (A), R43.1
unnamed: D13.1 (K), R29.1
unnamed: D14.1 (K), R30.1
unnamed: D16.1 (K), R32.1
unnamed: D17.2 (A), R42.1
unnamed: IC1.77 (ISET), R28.2
unnamed: IC1.25 (LED3_0), R41.2
unnamed: IC1.24 (LED3_1), R39.2
unnamed: IC1.79 (XI), Y1.3 (OUT)
unnamed: J2.10 (DAS/~DSS/~LED1), R1.2
unnamed: J2.68 (SUSCLK), U1.3 (Out)
unnamed: J10.9, R35.1
unnamed: J10.12, R27.1
unnamed: C25.1, J10.5 (RCT)
unnamed: C18.1, J10.4 (TCT)
unnamed: J18.9, R37.1
unnamed: J18.12, R36.1
unnamed: C23.1, J18.5 (RCT)
unnamed: C24.1, J18.4 (TCT)
unnamed: J25.1, U7.4 (GPB3)
unnamed: J25.2, U7.5 (GPB4)
unnamed: J25.3, U7.6 (GPB5)
unnamed: J25.4, U7.7 (GPB6)
unnamed: J25.5, U7.8 (GPB7)
unnamed: J25.11, U7.27 (GPA6)
unnamed: J25.12, U7.28 (GPA7)
unnamed: JP12.2 (C), U4.7 (EN)
unnamed: JP13.2 (C), U8.7 (EN)
unnamed: JP14.2 (C), U9.7 (EN)
unnamed: Q1.2 (G), U2.5 (GATE)
unnamed: Q2.2 (G), U3.5 (GATE)
unnamed: C46.1, TR1.4 (C_RD)
unnamed: C48.1, TR1.9 (C_RX)
unnamed: C45.1, TR1.3 (C_TD)
unnamed: C47.1, TR1.10 (C_TX)
unnamed: C54.1, U2.1 (VCAP)
unnamed: C55.1, U3.1 (VCAP)
unnamed: C57.2, U4.8 (NR/SS)
unnamed: R52.2, U5.31 (IO19)
unnamed: R53.2, U5.33 (IO21)
unnamed: R54.2, U5.36 (IO22)
unnamed: R55.2, U5.10 (IO25)
unnamed: R56.2, U5.11 (IO26)
unnamed: R57.2, U5.12 (IO27)
unnamed: R17.1, U6.5 (ILIM)
unnamed: C59.2, U8.8 (NR/SS)
unnamed: C63.2, U9.8 (NR/SS)
unnamed: R46.1, U10.16 (VPU)
unnamed: R47.1, U11.16 (VPU)

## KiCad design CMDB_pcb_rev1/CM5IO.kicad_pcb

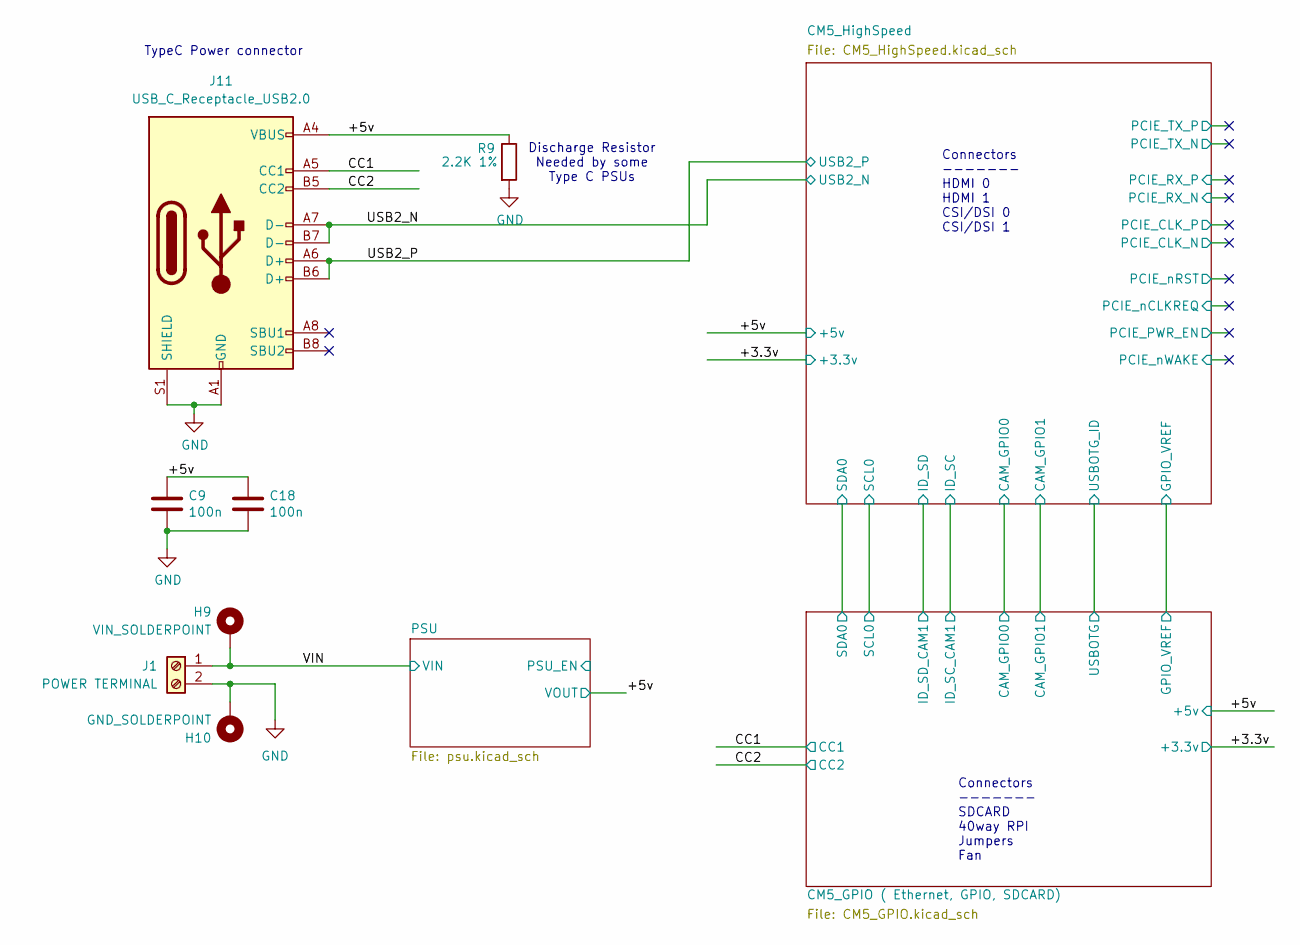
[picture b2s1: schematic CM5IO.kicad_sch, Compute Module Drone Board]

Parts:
C9, C18: 100n; C_0402_1005Metric; Part Description 0.1uF 10% 16V Ceramic Capacitor X7R 040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
H9: VIN_SOLDERPOINT; SolderWirePad_1x01_SMD_5x10mm
H10: GND_SOLDERPOINT; SolderWirePad_1x01_SMD_5x10mm
J1: POWER TERMINAL; TerminalBlock_bornier-2_P5.08mm
J11: USB_C_Receptacle_USB2.0; USB_C_Receptacle_GCT_USB4105-xx-A_16P_TopMnt_Horizontal; Part Description USBC USB2 data and power connector
R9: 2.2K 1%; R_0402_1005Metric; Part Description Resistor 2.2K M1005 1% 63mW

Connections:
/+5v: C9.1, C18.1, J11.A4 (VBUS), J11.A9 (VBUS), J11.B4 (VBUS), J11.B9 (VBUS), R9.1; also elsewhere on the board
/CC1: J11.A5 (CC1); also elsewhere on the board
/CC2: J11.B5 (CC2); also elsewhere on the board
/USB2_N: J11.A7 (D-), J11.B7 (D-); also elsewhere on the board
/USB2_P: J11.A6 (D+), J11.B6 (D+); also elsewhere on the board
/VIN: H9.1 (MP), J1.1; also elsewhere on the board
GND: C9.2, C18.2, H10.1 (MP), J1.2, J11.A1 (GND), J11.A12 (GND), J11.B1 (GND), J11.B12 (GND), J11.S1 (SHIELD), R9.2; also elsewhere on the board

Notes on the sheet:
Connectors ------- SDCARD 40way RPI Jumpers Fan
Discharge Resistor Needed by some Type C PSUs
TypeC Power connector
Connectors ------- HDMI 0 HDMI 1 CSI/DSI 0 CSI/DSI 1

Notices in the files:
CMDB_pcb/CM5_HighSpeed.kicad_sch:
Copyright © 2024 Raspberry Pi Ltd.
